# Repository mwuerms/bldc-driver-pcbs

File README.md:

# bldc-driver-pcbs

create simple bldc driver pcbs for these chips, start with simplest, then create a more complex one

1. DRV8317
1. DRV8304

also see: [docs/drivers](docs/drivers.md)

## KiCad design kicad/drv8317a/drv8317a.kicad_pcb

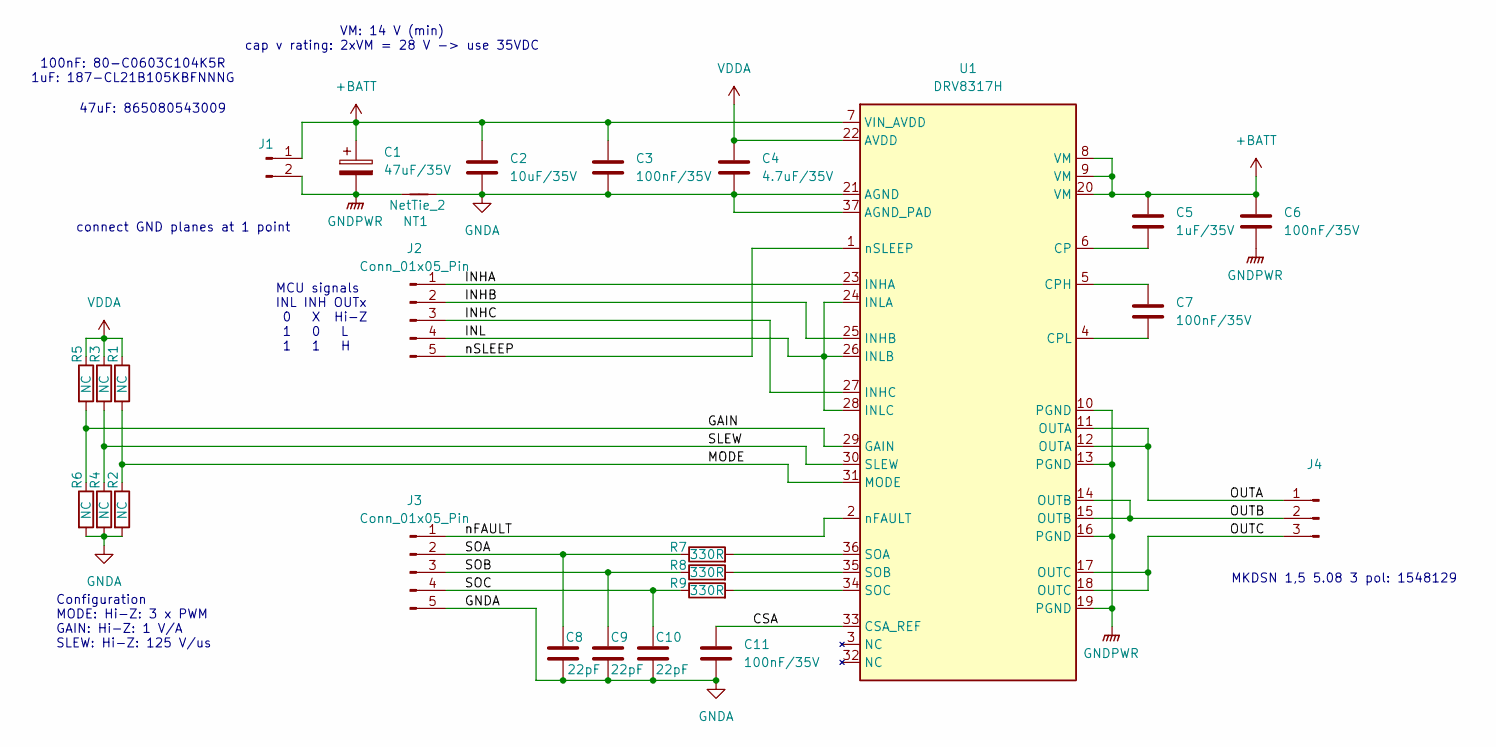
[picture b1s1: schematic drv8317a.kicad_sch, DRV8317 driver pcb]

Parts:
C1: 47uF/35V; CP_Elec_6.3x7.7
C2: 10uF/35V; C_0805_2012Metric_Pad1.18x1.45mm_HandSolder
C3, C6, C7, C11: 100nF/35V; C_0603_1608Metric_Pad1.08x0.95mm_HandSolder
C4: 4.7uF/35V; C_0805_2012Metric_Pad1.18x1.45mm_HandSolder
C5: 1uF/35V; C_0805_2012Metric_Pad1.18x1.45mm_HandSolder
C8, C9, C10: 22pF; C_0603_1608Metric_Pad1.08x0.95mm_HandSolder
J1: Conn_01x02_Pin; PinHeader_1x02_P2.54mm_Vertical
J2, J3: Conn_01x05_Pin; PinHeader_1x05_P2.54mm_Vertical
J4: Conn_01x03_Pin; TerminalBlock_Phoenix_MKDS-1,5-3-5.08_1x03_P5.08mm_Horizont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
NT1: NetTie_2; NetTie-2_SMD_Pad2.0mm
R1, R2, R3, R4, R5, R6: NC; R_0603_1608Metric_Pad0.98x0.95mm_HandSolder
R7, R8, R9: 330R; R_0603_1608Metric_Pad0.98x0.95mm_HandSolder
U1: DRV8317H; WQFN-36_EP_4.4x5.4_Pitch0.4mm

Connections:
+BATT: C1.1, C2.1, C3.1, C5.1, C6.1, J1.1, U1.7 (VIN_AVDD), U1.8 (VM), U1.9 (VM), U1.20 (VM)
/CSA: C11.1, U1.33 (CSA_REF)
/GAIN: R5.2, R6.1, U1.29 (GAIN)
/INHA: J2.1, U1.23 (INHA)
/INHB: J2.2, U1.25 (INHB)
/INHC: J2.3, U1.27 (INHC)
/INL: J2.4, U1.24 (INLA), U1.26 (INLB), U1.28 (INLC)
/MODE: R1.2, R2.1, U1.31 (MODE)
/OUTA: J4.1, U1.11 (OUTA), U1.12 (OUTA)
/OUTB: J4.2, U1.14 (OUTB), U1.15 (OUTB)
/OUTC: J4.3, U1.17 (OUTC), U1.18 (OUTC)
/SLEW: R3.2, R4.1, U1.30 (SLEW)
/SOA: C8.1, J3.2, R7.1
/SOB: C9.1, J3.3, R8.1
/SOC: C10.1, J3.4, R9.1
/nFAULT: J3.1, U1.2 (nFAULT)
/nSLEEP: J2.5, U1.1 (nSLEEP)
GNDA: C2.2, C3.2, C4.2, C8.2, C9.2, C10.2, C11.2, J3.5, NT1.2, R2.2, R4.2, R6.2, U1.21 (AGND), U1.37 (AGND_PAD)
GNDPWR: C1.2, C6.2, J1.2, NT1.1, U1.10 (PGND), U1.13 (PGND), U1.16 (PGND), U1.19 (PGND)
unnamed: C5.2, U1.6 (CP)
unnamed: C7.1, U1.5 (CPH)
unnamed: C7.2, U1.4 (CPL)
unnamed: R7.2, U1.36 (SOA)
unnamed: R8.2, U1.35 (SOB)
unnamed: R9.2, U1.34 (SOC)
VDDA: C4.1, R1.1, R3.1, R5.1, U1.22 (AVDD)

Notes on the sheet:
MKDSN 1,5 5.08 3 pol: 1548129
VM: 14 V (min) cap v rating: 2xVM = 28 V -> use 35VDC
MCU signals INL INH OUTx 0 X Hi-Z 1 0 L 1 1 H
Configuration MODE: Hi-Z: 3 x PWM GAIN: Hi-Z: 1 V/A SLEW: Hi-Z: 125 V/us
47uF: 865080543009
100nF: 80-C0603C104K5R 1uF: 187-CL21B105KBFNNNG
connect GND planes at 1 point

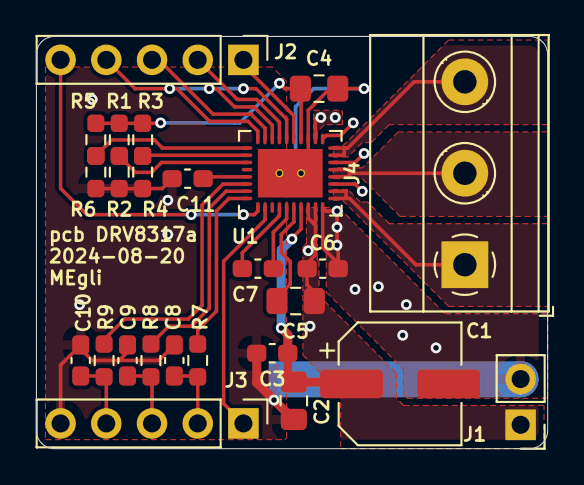
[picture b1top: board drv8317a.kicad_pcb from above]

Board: 2 copper layers, 28.4 x 22.9 mm, 26 parts (1 on the bottom side), 26 nets.

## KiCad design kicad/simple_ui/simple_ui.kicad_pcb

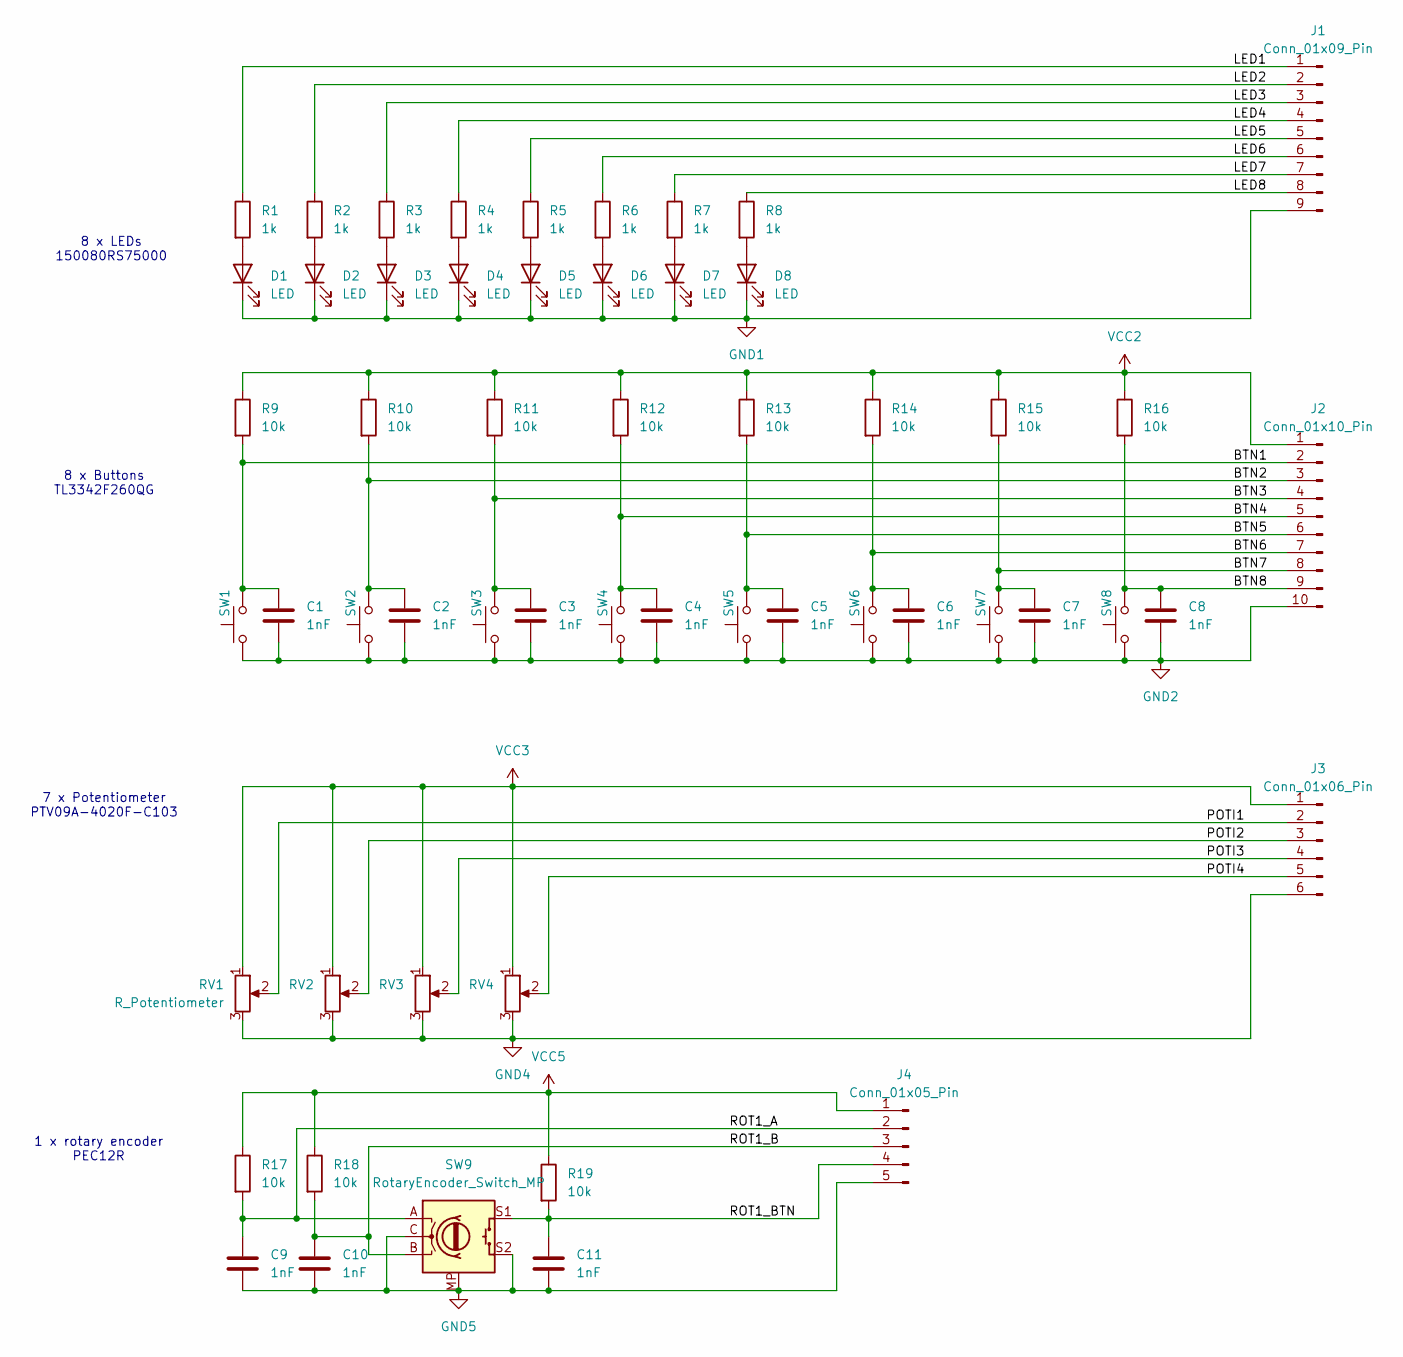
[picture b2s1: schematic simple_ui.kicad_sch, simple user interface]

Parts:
C1, C2, C3, C4, C5, C6, C7, C8, C9, C10, C11: 1nF; C_0603_1608Metric_Pad1.08x0.95mm_HandSolder
D1, D2, D3, D4, D5, D6, D7, D8: LED; LED_0805_2012Metric_Pad1.15x1.40mm_HandSolder
J1: Conn_01x09_Pin; PinSocket_1x09_P1.27mm_Vertical
J2: Conn_01x10_Pin; PinSocket_1x10_P1.27mm_Vertical
J3: Conn_01x06_Pin; PinSocket_1x06_P1.27mm_Vertical
J4: Conn_01x05_Pin; PinSocket_1x05_P1.27mm_Vertical
R1, R2, R3, R4, R5, R6, R7, R8: 1k; R_0603_1608Metric_Pad0.98x0.95mm_HandSolder
R9, R10, R11, R12, R13, R14, R15, R16, R17, R18, R19: 10k; R_0603_1608Metric_Pad0.98x0.95mm_HandSolder
RV1, RV2, RV3, RV4: R_Potentiometer; Potentiometer_Bourns_PTV09A-1_Single_Vertical
SW1, SW2, SW3, SW4, SW5, SW6, SW7, SW8: SW_Push; SW_SPST_TL3342
SW9: RotaryEncoder_Switch_MP; RotaryEncoder_Bourns_Vertical_PEC12R-3x17F-Sxxxx

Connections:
/BTN1: C1.1, J2.2, R9.2, SW1.2
/BTN2: C2.1, J2.3, R10.2, SW2.2
/BTN3: C3.1, J2.4, R11.2, SW3.2
/BTN4: C4.1, J2.5, R12.2, SW4.2
/BTN5: C5.1, J2.6, R13.2, SW5.2
/BTN6: C6.1, J2.7, R14.2, SW6.2
/BTN7: C7.1, J2.8, R15.2, SW7.2
/BTN8: C8.1, J2.9, R16.2, SW8.2
/LED1: J1.1, R1.1
/LED2: J1.2, R2.1
/LED3: J1.3, R3.1
/LED4: J1.4, R4.1
/LED5: J1.5, R5.1
/LED6: J1.6, R6.1
/LED7: J1.7, R7.1
/LED8: J1.8, R8.1
/POTI1: J3.2, RV1.2
/POTI2: J3.3, RV2.2
/POTI3: J3.4, RV3.2
/POTI4: J3.5, RV4.2
/ROT1_A: C9.1, J4.2, R17.2, SW9.A
/ROT1_B: C10.1, J4.3, R18.2, SW9.B
/ROT1_BTN: C11.1, J4.4, R19.2, SW9.S1
GND1: D1.1 (K), D2.1 (K), D3.1 (K), D4.1 (K), D5.1 (K), D6.1 (K), D7.1 (K), D8.1 (K), J1.9
GND2: C1.2, C2.2, C3.2, C4.2, C5.2, C6.2, C7.2, C8.2, J2.10, SW1.1, SW2.1, SW3.1, SW4.1, SW5.1, SW6.1, SW7.1, SW8.1
GND4: J3.6, RV1.3, RV2.3, RV3.3, RV4.3
GND5: C9.2, C10.2, C11.2, J4.5, SW9.C, SW9.MP, SW9.S2
unnamed: D1.2 (A), R1.2
unnamed: D2.2 (A), R2.2
unnamed: D3.2 (A), R3.2
unnamed: D4.2 (A), R4.2
unnamed: D5.2 (A), R5.2
unnamed: D6.2 (A), R6.2
unnamed: D7.2 (A), R7.2
unnamed: D8.2 (A), R8.2
VCC2: J2.1, R9.1, R10.1, R11.1, R12.1, R13.1, R14.1, R15.1, R16.1
VCC3: J3.1, RV1.1, RV2.1, RV3.1, RV4.1
VCC5: J4.1, R17.1, R18.1, R19.1

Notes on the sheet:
8 x LEDs 150080RS75000
7 x Potentiometer PTV09A-4020F-C103
8 x Buttons TL3342F260QG
1 x rotary encoder PEC12R

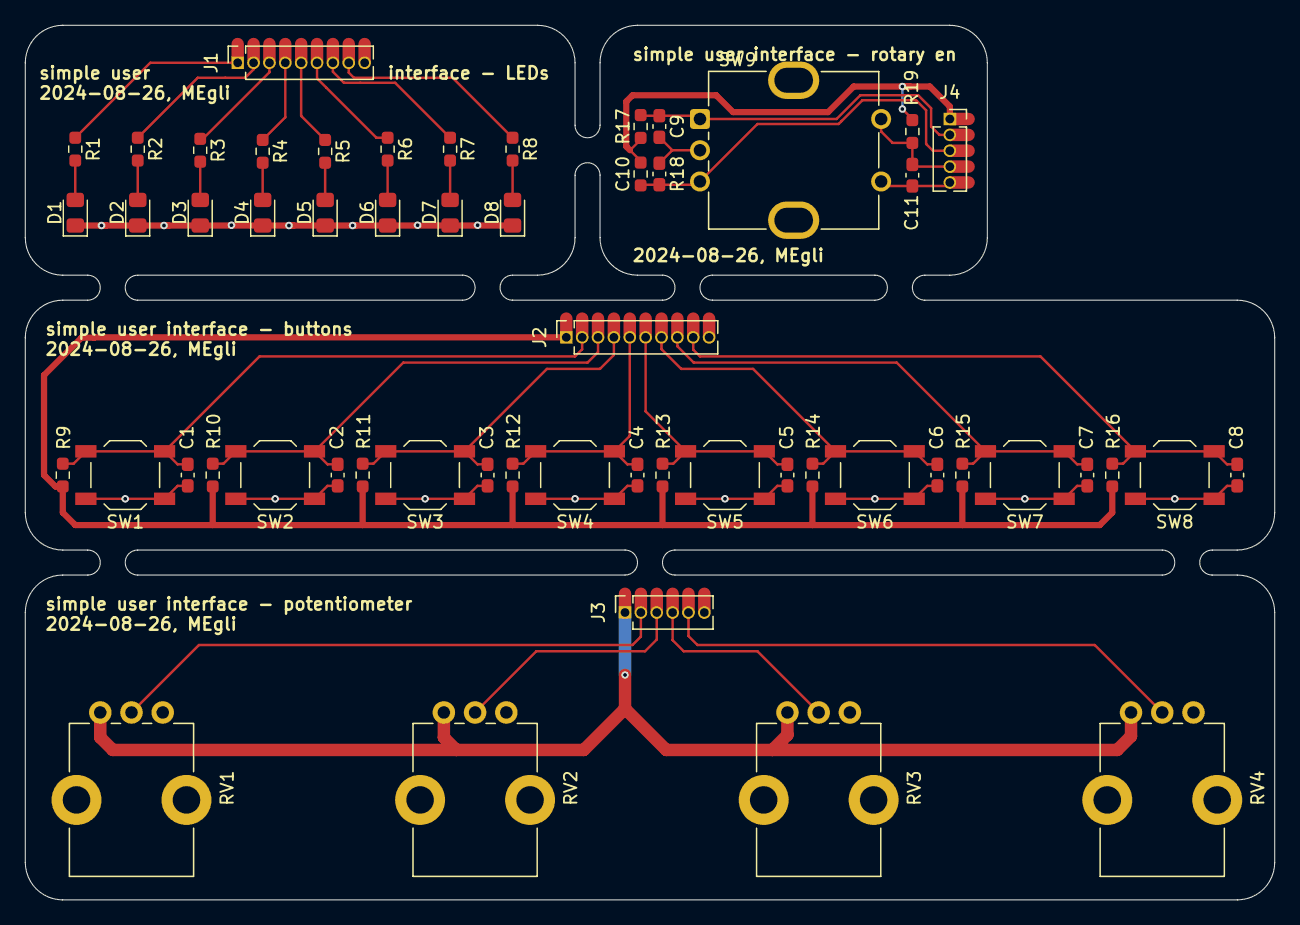
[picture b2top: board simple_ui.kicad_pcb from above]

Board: 2 copper layers, 100.0 x 70.0 mm, 55 parts (0 on the bottom side), 38 nets.

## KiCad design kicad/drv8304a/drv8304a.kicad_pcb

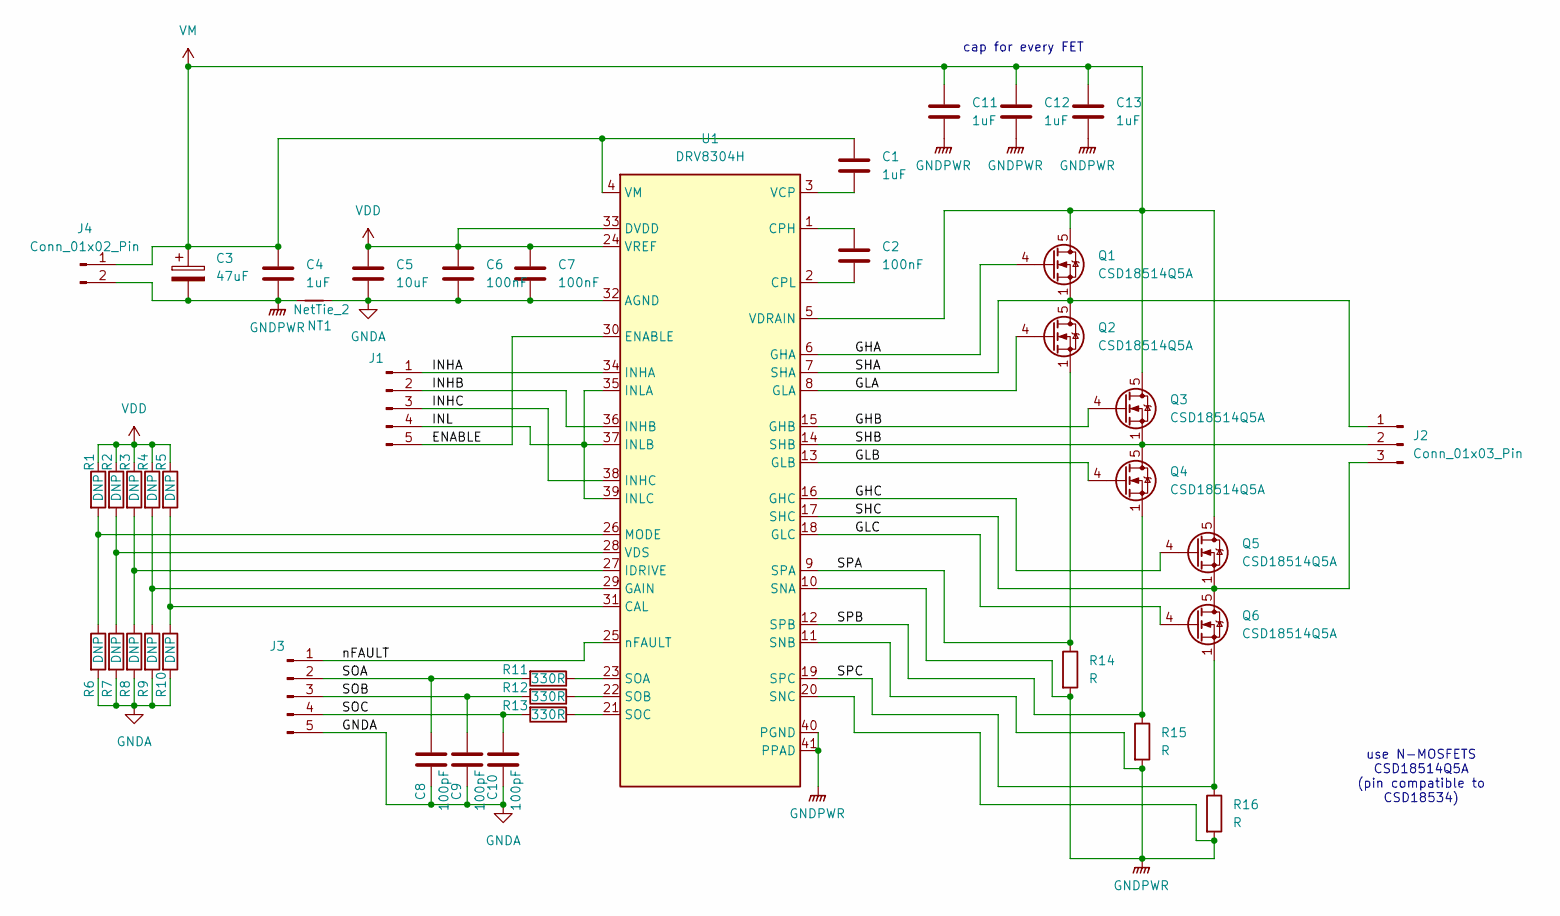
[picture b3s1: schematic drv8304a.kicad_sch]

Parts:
C1, C4, C11, C12, C13: 1uF; C_0805_2012Metric_Pad1.18x1.45mm_HandSolder
C2, C6, C7: 100nF; C_0603_1608Metric_Pad1.08x0.95mm_HandSolder
C3: 47uF; CP_Elec_6.3x7.7
C5: 10uF; C_0805_2012Metric_Pad1.18x1.45mm_HandSolder
C8, C9, C10: 100pF; C_0603_1608Metric_Pad1.08x0.95mm_HandSolder
J1, J3: Conn_01x05_Pin; PinHeader_1x05_P2.54mm_Vertical
J2: Conn_01x03_Pin; TerminalBlock_Phoenix_MKDS-1,5-3-5.08_1x03_P5.08mm_Horizont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
J4: Conn_01x02_Pin; TerminalBlock_Phoenix_MKDS-1,5-2_1x02_P5.00mm_Horizontal
NT1: NetTie_2; NetTie-2_SMD_Pad2.0mm
Q1, Q2, Q3, Q4, Q5, Q6: CSD18514Q5A; TDSON-8-1
R1, R2, R3, R4, R5, R6, R7, R8, R9, R10: DNP; R_0603_1608Metric_Pad0.98x0.95mm_HandSolder
R11, R12, R13: 330R; R_0603_1608Metric_Pad0.98x0.95mm_HandSolder
R14, R15, R16: R; R_2512_6332Metric_Pad1.40x3.35mm_HandSolder
U1: DRV8304H; Texas_RHA0040E_VQFN-40-1EP_6x6mm_P0.5mm_EP3.52x2.62mm

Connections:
/ENABLE: J1.5, U1.30 (ENABLE)
/GHA: Q1.4 (G), U1.6 (GHA)
/GHB: Q3.4 (G), U1.15 (GHB)
/GHC: Q5.4 (G), U1.16 (GHC)
/GLA: Q2.4 (G), U1.8 (GLA)
/GLB: Q4.4 (G), U1.13 (GLB)
/GLC: Q6.4 (G), U1.18 (GLC)
/INHA: J1.1, U1.34 (INHA)
/INHB: J1.2, U1.36 (INHB)
/INHC: J1.3, U1.38 (INHC)
/INL: J1.4, U1.35 (INLA), U1.37 (INLB), U1.39 (INLC)
/SHA: J2.1, Q1.1 (S), Q1.2 (S), Q1.3 (S), Q2.5 (D), U1.7 (SHA)
/SHB: J2.2, Q3.1 (S), Q3.2 (S), Q3.3 (S), Q4.5 (D), U1.14 (SHB)
/SHC: J2.3, Q5.1 (S), Q5.2 (S), Q5.3 (S), Q6.5 (D), U1.17 (SHC)
/SOA: C8.1, J3.2, R11.2
/SOB: C9.1, J3.3, R12.2
/SOC: C10.1, J3.4, R13.2
/SPA: Q2.1 (S), Q2.2 (S), Q2.3 (S), R14.1, U1.9 (SPA)
/SPB: Q4.1 (S), Q4.2 (S), Q4.3 (S), R15.1, U1.12 (SPB)
/SPC: Q6.1 (S), Q6.2 (S), Q6.3 (S), R16.1, U1.19 (SPC)
/nFAULT: J3.1, U1.25 (nFAULT)
GNDA: C5.2, C6.2, C7.2, C8.2, C9.2, C10.2, J3.5, NT1.2, R6.2, R7.2, R8.2, R9.2, R10.2, U1.32 (AGND)
GNDPWR: C3.2, C4.2, C11.2, C12.2, C13.2, J4.2, NT1.1, R14.2, R15.2, R16.2, U1.10 (SNA), U1.11 (SNB), U1.20 (SNC), U1.40 (PGND), U1.41 (PPAD)
unnamed: R5.2, R10.1, U1.31 (CAL)
unnamed: C2.1, U1.1 (CPH)
unnamed: C2.2, U1.2 (CPL)
unnamed: R4.2, R9.1, U1.29 (GAIN)
unnamed: R3.2, R8.1, U1.27 (IDRIVE)
unnamed: R1.2, R6.1, U1.26 (MODE)
unnamed: R11.1, U1.23 (SOA)
unnamed: R12.1, U1.22 (SOB)
unnamed: R13.1, U1.21 (SOC)
unnamed: C1.2, U1.3 (VCP)
unnamed: R2.2, R7.1, U1.28 (VDS)
VDD: C5.1, C6.1, C7.1, R1.1, R2.1, R3.1, R4.1, R5.1, U1.24 (VREF), U1.33 (DVDD)
VM: C1.1, C3.1, C4.1, C11.1, C12.1, C13.1, J4.1, Q1.5 (D), Q3.5 (D), Q5.5 (D), U1.4 (VM), U1.5 (VDRAIN)

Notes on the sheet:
cap for every FET
use N-MOSFETS CSD18514Q5A (pin compatible to CSD18534)

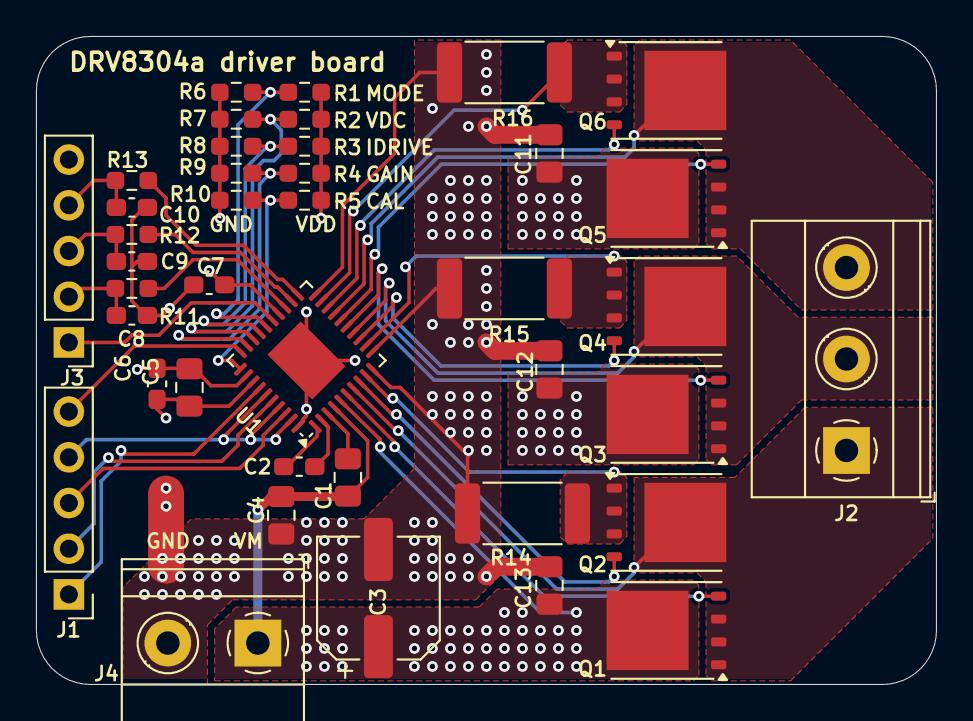
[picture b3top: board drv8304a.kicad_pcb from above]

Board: 4 copper layers, 50.0 x 36.0 mm, 41 parts (0 on the bottom side), 36 nets.

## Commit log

2024-08-16 decide to create DFV8317 first
2024-08-16 started kicad project
2024-08-17 added DRV8317
2024-08-17 WQFN 36 Footprint added
2024-08-17 pcb started
2024-08-18 100% routed, review needed
2024-08-18 config: use resistors instead of mcu signals
2024-08-21 pcb DRV8317a all done
2024-08-25 started a simple user interface pcb: LEDs, potim buttons, rotary encoders
2024-08-26 simple ui done
2024-08-26 started DRV8304 rev a pcb
2024-08-27 DRV8304a schematics done, starting layout
2024-08-27 some routing
2024-08-27 FETS routed
2024-08-27 lots routed
2024-08-28 100 % routed, supply layer thickend
2024-08-29 DRV8304a done
2024-08-29 ready to order pcbs
2024-10-23 drc8317a added small description for printing
